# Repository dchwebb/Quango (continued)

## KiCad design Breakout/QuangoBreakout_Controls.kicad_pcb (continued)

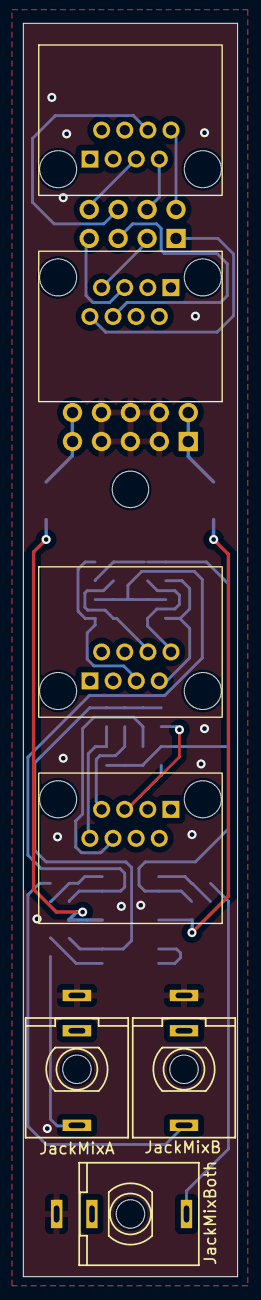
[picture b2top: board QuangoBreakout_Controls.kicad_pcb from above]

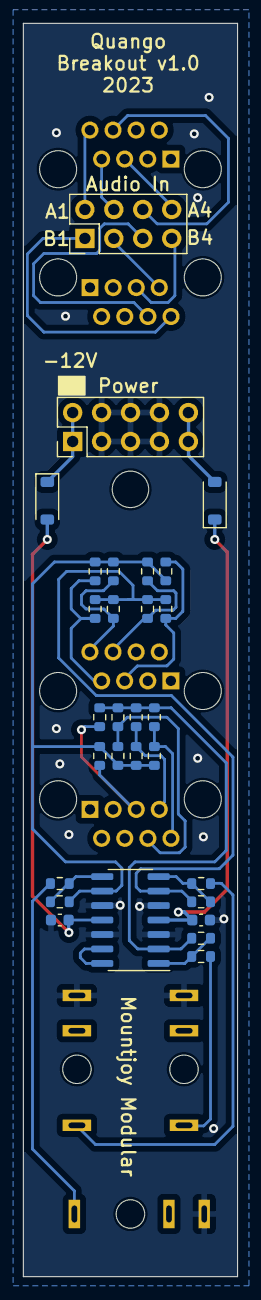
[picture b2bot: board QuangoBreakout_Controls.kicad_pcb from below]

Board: 2 copper layers, 18.8 x 110.0 mm, 37 parts (29 on the bottom side), 31 nets.

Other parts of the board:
H1: MountingHole; MountingHole_3.2mm_M3_ISO14580

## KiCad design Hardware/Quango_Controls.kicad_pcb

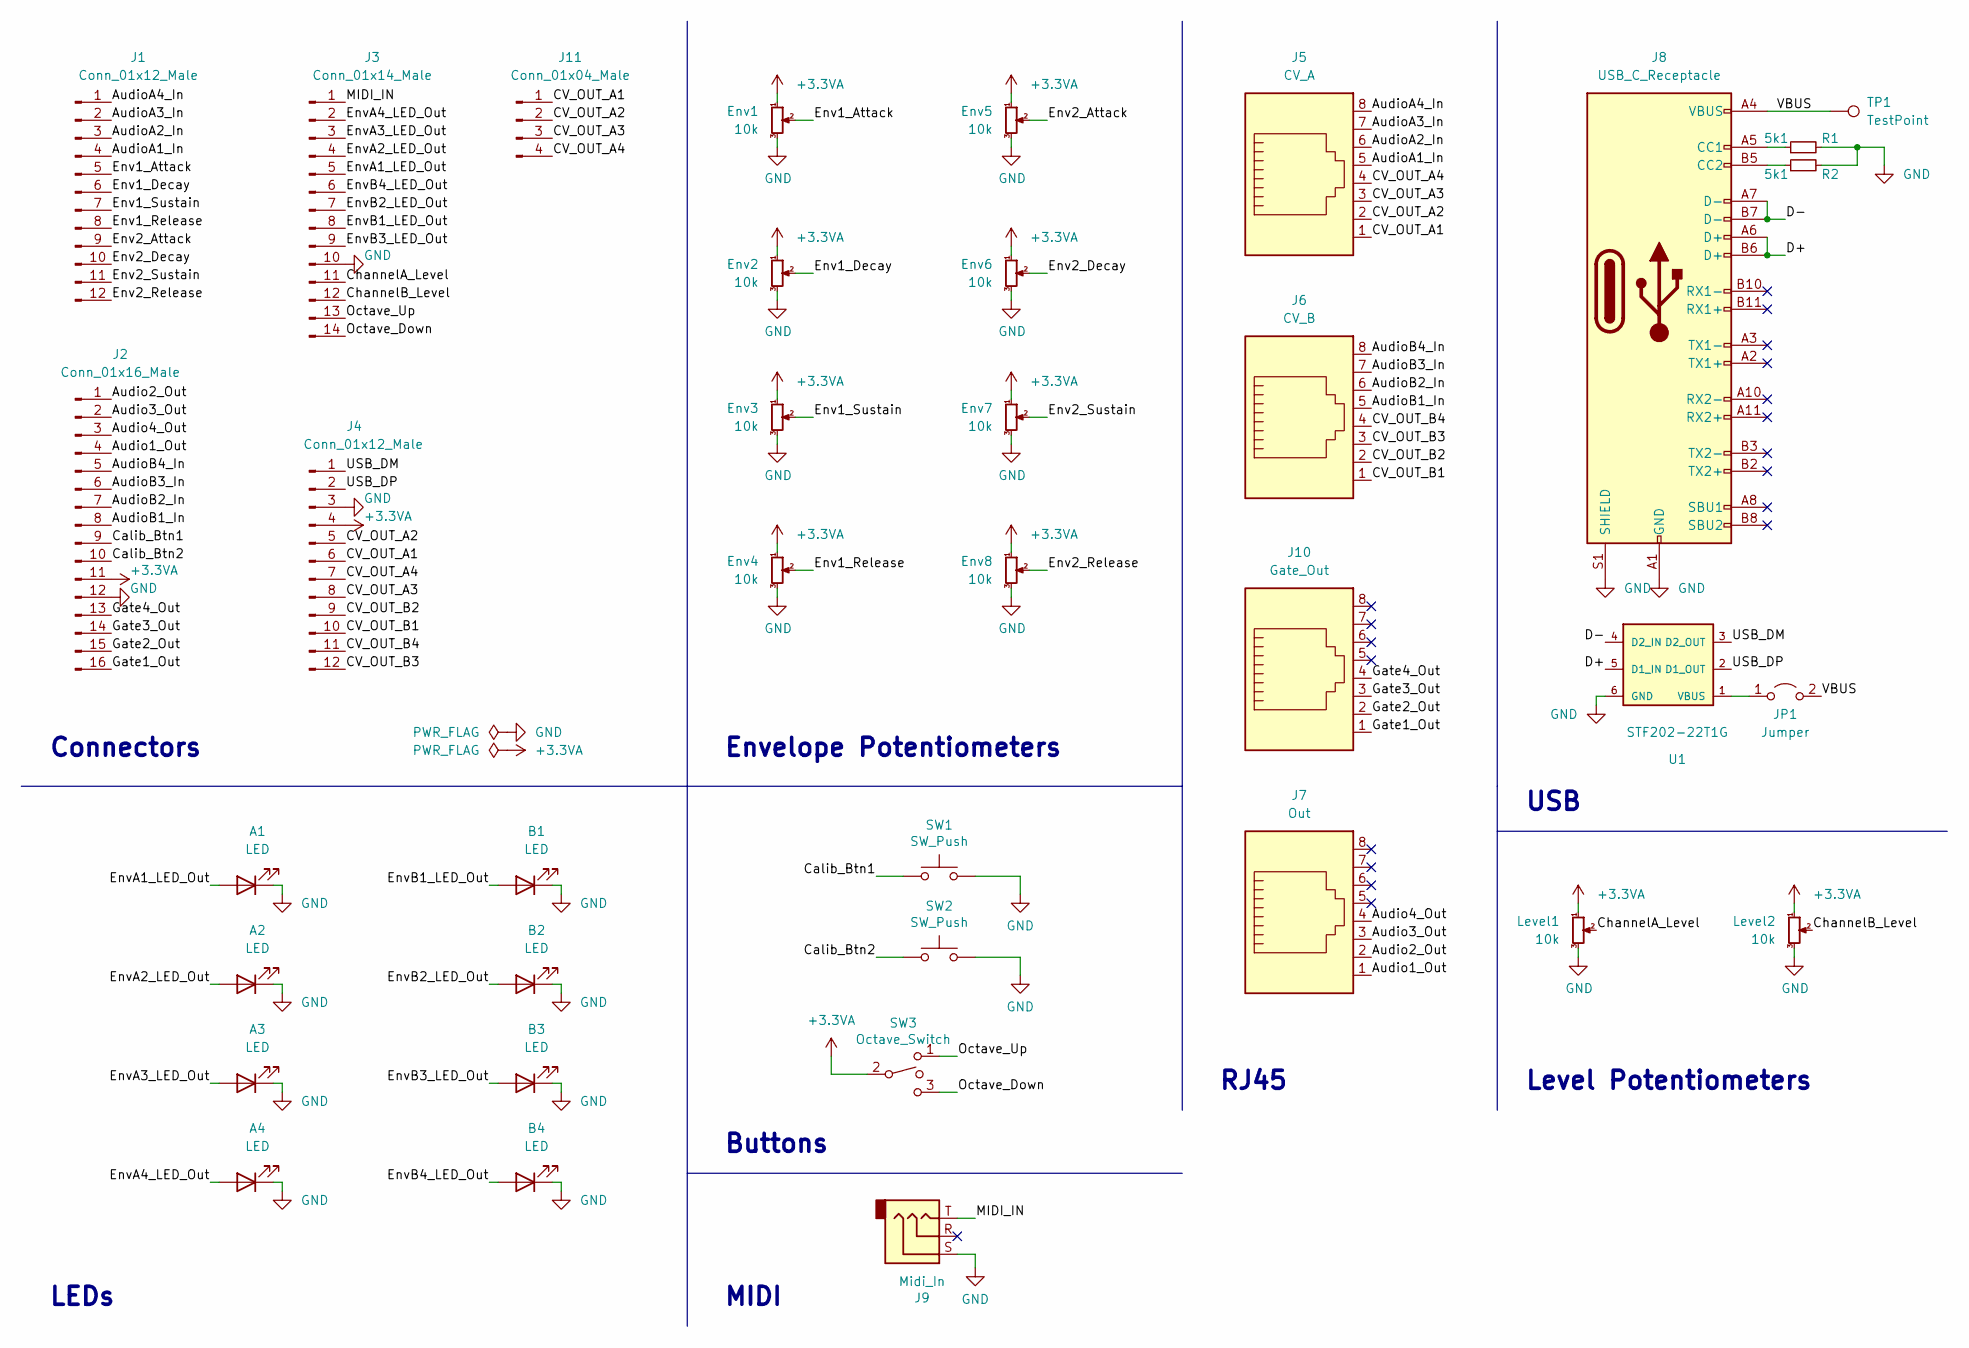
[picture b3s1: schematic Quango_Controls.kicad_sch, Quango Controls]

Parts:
A1, A2, A3, A4: LED; LED_D3.0mm
B1, B2, B3, B4: LED; LED_D3.0mm
Env1, Env2, Env3, Env4, Env5, Env6, Env7, Env8: 10k; Alpha_9mm_Potentiometer_Aligned
J1, J4: Conn_01x12_Male; PinSocket_1x12_P2.54mm_Vertical
J2: Conn_01x16_Male; PinSocket_1x16_P2.54mm_Vertical
J3: Conn_01x14_Male; PinSocket_1x14_P2.54mm_Vertical
J5: CV_A; RJ45_Molex_42878-8506
J6: CV_B; RJ45_Molex_42878-8506
J7: Out; RJ45_Molex_42878-8506
J8: USB_C_Receptacle; USB_C_Receptacle_Amphenol_12401951E412A
J9: Midi_In; Thonkiconn_Stereo-PJ366ST
J10: Gate_Out; RJ45_Molex_42878-8506
J11: Conn_01x04_Male; PinHeader_1x04_P2.54mm_Vertical
JP1: Jumper; SolderJumper-2_P1.3mm_Open_RoundedPad1.0x1.5mm
Level1, Level2: 10k; Potentiometer_Bourns_PTA4543_Single_Slide
R1, R2: 5k1; R_0805_2012Metric
SW1, SW2: SW_Push; SW_PUSH_6mm_aligned
SW3: Octave_Switch; SP3T_Mini_Switch
TP1: TestPoint; PinSocket_1x01_P2.54mm_Vertical
U1: STF202-22T1G

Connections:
+3.3VA: Env1.1, Env2.1, Env3.1, Env4.1, Env5.1, Env6.1, Env7.1, Env8.1, J2.11, J4.4, Level1.1, Level2.1, SW3.2
/Audio1_Out: J2.4, J7.1
/Audio2_Out: J2.1, J7.2
/Audio3_Out: J2.2, J7.3
/Audio4_Out: J2.3, J7.4
/AudioA1_In: J1.4, J5.5
/AudioA2_In: J1.3, J5.6
/AudioA3_In: J1.2, J5.7
/AudioA4_In: J1.1, J5.8
/AudioB1_In: J2.8, J6.5
/AudioB2_In: J2.7, J6.6
/AudioB3_In: J2.6, J6.7
/AudioB4_In: J2.5, J6.8
/CV_OUT_A1: J4.6, J5.1, J11.1
/CV_OUT_A2: J4.5, J5.2, J11.2
/CV_OUT_A3: J4.8, J5.3, J11.3
/CV_OUT_A4: J4.7, J5.4, J11.4
/CV_OUT_B1: J4.10, J6.1
/CV_OUT_B2: J4.9, J6.2
/CV_OUT_B3: J4.12, J6.3
/CV_OUT_B4: J4.11, J6.4
/Calib_Btn1: J2.9, SW1.1
/Calib_Btn2: J2.10, SW2.1
/ChannelA_Level: J3.11, Level1.2
/ChannelB_Level: J3.12, Level2.2
/D+: J8.A6 (D+), J8.B6 (D+), U1.5 (D1_IN)
/D-: J8.A7 (D-), J8.B7 (D-), U1.4 (D2_IN)
/Env1_Attack: Env1.2, J1.5
/Env1_Decay: Env2.2, J1.6
/Env1_Release: Env4.2, J1.8
/Env1_Sustain: Env3.2, J1.7
/Env2_Attack: Env5.2, J1.9
/Env2_Decay: Env6.2, J1.10
/Env2_Release: Env8.2, J1.12
/Env2_Sustain: Env7.2, J1.11
/EnvA1_LED_Out: A1.2 (A), J3.5
/EnvA2_LED_Out: A2.2 (A), J3.4
/EnvA3_LED_Out: A3.2 (A), J3.3
/EnvA4_LED_Out: A4.2 (A), J3.2
/EnvB1_LED_Out: B1.2 (A), J3.8
/EnvB2_LED_Out: B2.2 (A), J3.7
/EnvB3_LED_Out: B3.2 (A), J3.9
/EnvB4_LED_Out: B4.2 (A), J3.6
/Gate1_Out: J2.16, J10.1
/Gate2_Out: J2.15, J10.2
/Gate3_Out: J2.14, J10.3
/Gate4_Out: J2.13, J10.4
/MIDI_IN: J3.1, J9.T
/Octave_Down: J3.14, SW3.3
/Octave_Up: J3.13, SW3.1
/USB_DM: J4.1, U1.3 (D2_OUT)
/USB_DP: J4.2, U1.2 (D1_OUT)
/VBUS: J8.A4 (VBUS), J8.A9 (VBUS), J8.B4 (VBUS), J8.B9 (VBUS), JP1.2 (B), TP1.1
GND: A1.1 (K), A2.1 (K), A3.1 (K), A4.1 (K), B1.1 (K), B2.1 (K), B3.1 (K), B4.1 (K), Env1.3, Env2.3, Env3.3, Env4.3, Env5.3, Env6.3, Env7.3, Env8.3, J2.12, J3.10, J4.3, J8.A1 (GND), J8.A12 (GND), J8.B1 (GND), J8.B12 (GND), J8.S1 (SHIELD), J9.S, Level1.3, Level2.3, R1.2, R2.2, SW1.2, SW2.2, U1.6 (GND)
unnamed: J8.A5 (CC1), R1.1
unnamed: J8.B5 (CC2), R2.1
unnamed: JP1.1 (A), U1.1 (VBUS)

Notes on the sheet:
Buttons
Connectors
RJ45
USB
Level Potentiometers
Envelope Potentiometers
LEDs
MIDI

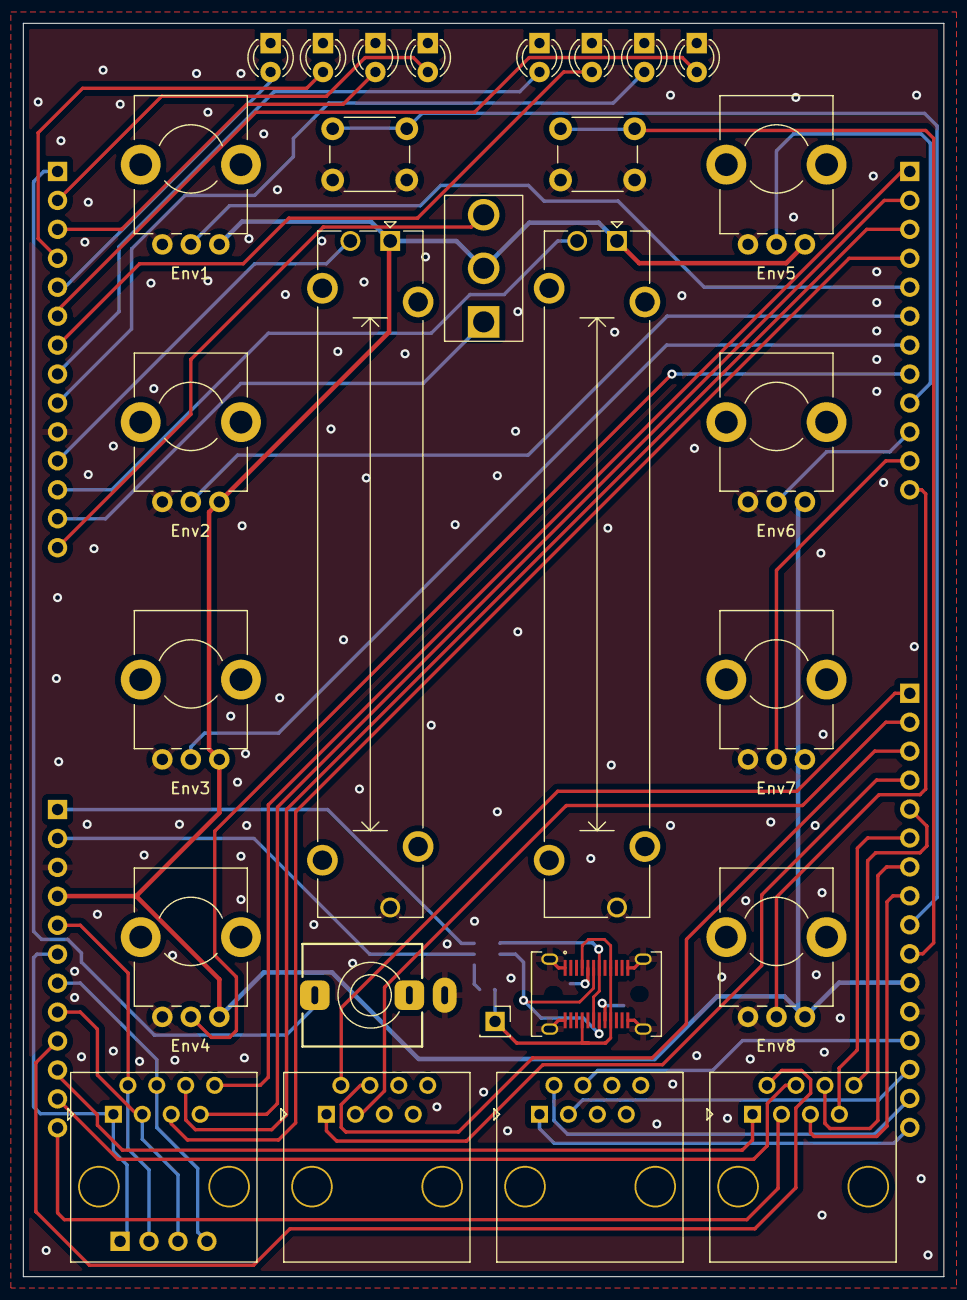
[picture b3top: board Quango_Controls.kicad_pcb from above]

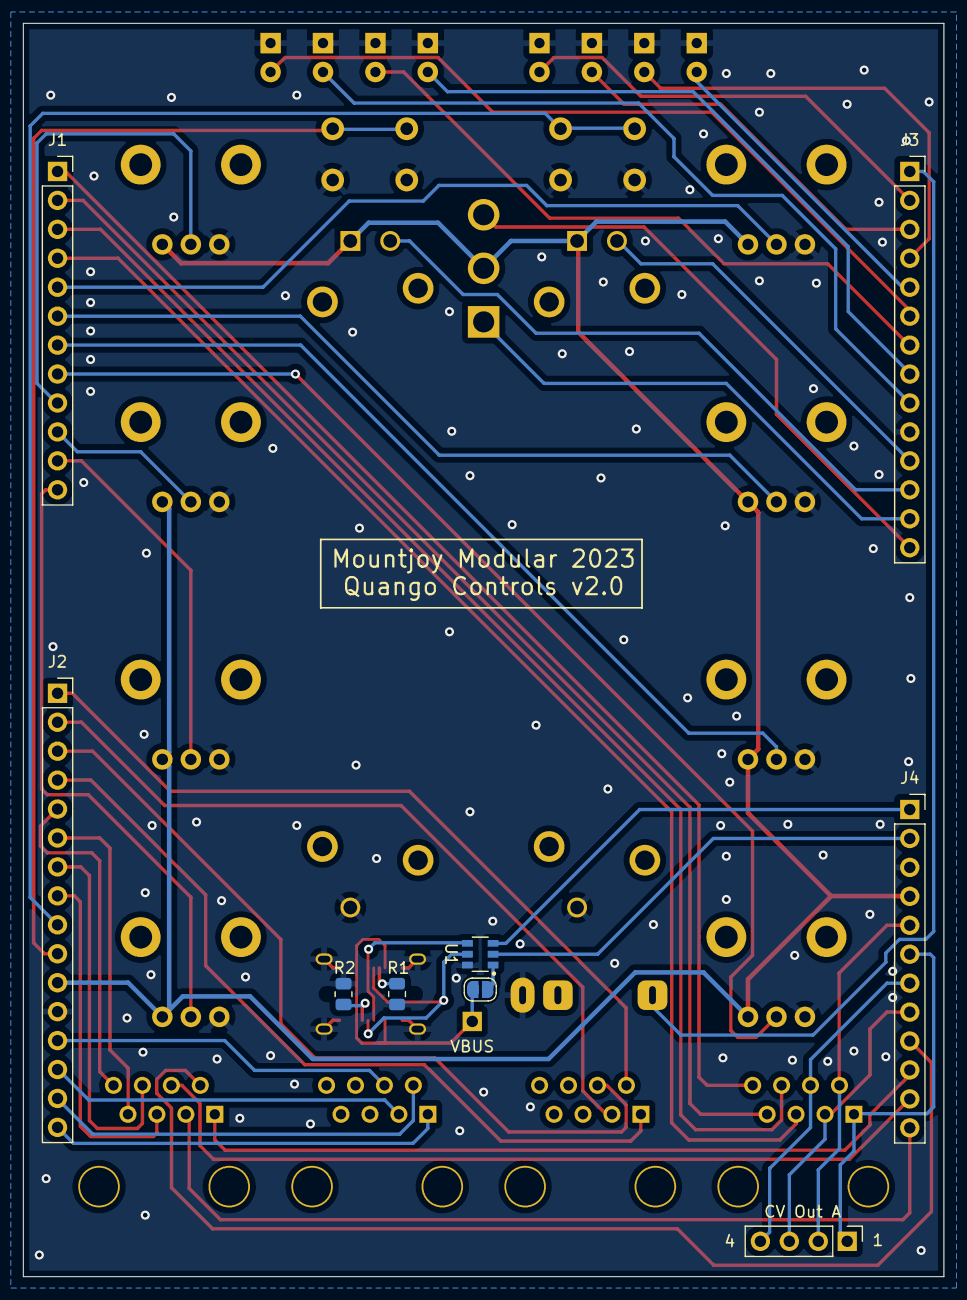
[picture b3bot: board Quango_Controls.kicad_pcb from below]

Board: 2 copper layers, 80.8 x 110.0 mm, 37 parts (9 on the bottom side), 57 nets.

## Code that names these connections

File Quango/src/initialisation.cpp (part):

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
void InitDAC()
{
	// Configure 4 DAC outputs PA4 and PA5 are regular DAC1 buffered outputs; PA2 and PB1 are DAC3 via OpAmp1 and OpAmp3 (Manual p.782)

	RCC->AHB2ENR |= RCC_AHB2ENR_GPIOAEN;			// Enable GPIO Clock
	RCC->AHB2ENR |= RCC_AHB2ENR_GPIOBEN;			// Enable GPIO Clock
	RCC->AHB2ENR |= RCC_AHB2ENR_DAC1EN | RCC_AHB2ENR_DAC2EN | RCC_AHB2ENR_DAC3EN | RCC_AHB2ENR_DAC4EN;				// Enable DAC Clock

	DAC1->MCR &= ~DAC_MCR_MODE1_Msk;				// Set to normal mode: DAC1 channel1 is connected to external pin with Buffer enabled
	DAC1->CR |= DAC_CR_EN1;							// Enable DAC using PA4 (DAC_OUT1)

	DAC1->MCR &= ~DAC_MCR_MODE2_Msk;				// Set to normal mode: DAC1 channel2 is connected to external pin with Buffer enabled
	DAC1->CR |= DAC_CR_EN2;							// Enable DAC using PA5 (DAC_OUT2)

	DAC2->MCR &= ~DAC_MCR_MODE1_Msk;				// Set to normal mode: DAC2 channel1 is connected to external pin with Buffer enabled
	DAC2->CR |= DAC_CR_EN1;							// Enable DAC using PA6 (DAC_OUT1)

	// output triggered with DAC->DHR12R1 = x;

	// Opamp for DAC3 Channel 1: Follower configuration mode - output on PA2
	DAC3->MCR |= DAC_MCR_MODE1_0 | DAC_MCR_MODE1_1;	// 011: DAC channel1 is connected to on chip peripherals with Buffer disabled
	DAC3->CR |= DAC_CR_EN1;							// Enable DAC

	OPAMP1->CSR |= OPAMP_CSR_VMSEL;					// 11: Opamp_out connected to OPAMPx_VINM input
	OPAMP1->CSR |= OPAMP_CSR_VPSEL;					// 11: DAC3_CH1  connected to OPAMP1 VINP input
	OPAMP1->CSR |= OPAMP_CSR_OPAMPxEN;				// Enable OpAmp: voltage on pin OPAMPx_VINP is buffered to pin OPAMPx_VOUT (PA2)

	// Opamp for DAC3 Channel 2: Follower configuration mode - output on PB1
	DAC3->MCR |= DAC_MCR_MODE2_0 | DAC_MCR_MODE2_1;	// 011: DAC channel2 is connected to on chip peripherals with Buffer disabled
	DAC3->CR |= DAC_CR_EN2;							// Enable DAC

	OPAMP3->CSR |= OPAMP_CSR_VMSEL;					// 11: Opamp_out connected to OPAMPx_VINM input
	OPAMP3->CSR |= OPAMP_CSR_VPSEL;					// 11: DAC3_CH2  connected to OPAMP1 VINP input
	OPAMP3->CSR |= OPAMP_CSR_OPAMPxEN;				// Enable OpAmp: voltage on pin OPAMPx_VINP is buffered to pin OPAMPx_VOUT (PB1)

	// Opamp for DAC4 Channel 1: Follower configuration mode - output on PB12
	DAC4->MCR |= DAC_MCR_MODE1_0 | DAC_MCR_MODE1_1;	// 011: DAC channel1 is connected to on chip peripherals with Buffer disabled
	DAC4->CR |= DAC_CR_EN1;							// Enable DAC

	OPAMP4->CSR |= OPAMP_CSR_VMSEL;					// 11: Opamp_out connected to OPAMPx_VINM input
	OPAMP4->CSR |= OPAMP_CSR_VPSEL;					// 11: DAC4_CH1  connected to OPAMP1 VINP input
	OPAMP4->CSR |= OPAMP_CSR_OPAMPxEN;				// Enable OpAmp: voltage on pin OPAMPx_VINP is buffered to pin OPAMPx_VOUT (PB12)

	// Opamp for DAC4 Channel 2: Follower configuration mode - output on PA8
	DAC4->MCR |= DAC_MCR_MODE2_0 | DAC_MCR_MODE2_1;	// 011: DAC channel2 is connected to on chip peripherals with Buffer disabled
	DAC4->CR |= DAC_CR_EN2;							// Enable DAC

	OPAMP5->CSR |= OPAMP_CSR_VMSEL;					// 11: Opamp_out connected to OPAMPx_VINM input
	OPAMP5->CSR |= OPAMP_CSR_VPSEL;					// 11: DAC4_CH2  connected to OPAMP1 VINP input
	OPAMP5->CSR |= OPAMP_CSR_OPAMPxEN;				// Enable OpAmp: voltage on pin OPAMPx_VINP is buffered to pin OPAMPx_VOUT (PA8)

}

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	RCC->AHB2ENR |= RCC_AHB2ENR_GPIODEN;			// GPIO D clock
	RCC->AHB2ENR |= RCC_AHB2ENR_GPIOFEN;			// GPIO F clock

	//	Init Multiplexer pins PA1, PA3, PF2
	GPIOA->MODER &= ~GPIO_MODER_MODER1_1;			// PA1: Multiplexer A0 out
	GPIOA->MODER &= ~GPIO_MODER_MODER3_1;			// PA3: Multiplexer A1 out
	GPIOF->MODER &= ~GPIO_MODER_MODER2_1;			// PF2: Multiplexer A2 out

	// Init Gate outputs PD2 - PD5
	GPIOD->MODER &= ~GPIO_MODER_MODER2_1;			// PD2: Gate1 Out
	GPIOD->MODER &= ~GPIO_MODER_MODER3_1;			// PD3: Gate2 Out
	GPIOD->MODER &= ~GPIO_MODER_MODER4_1;			// PD4: Gate3 Out
	GPIOD->MODER &= ~GPIO_MODER_MODER5_1;			// PD5: Gate4 Out

	// Calibration buttons input
	GPIOB->MODER &= ~GPIO_MODER_MODER10;			// PB10: channel A
	GPIOB->PUPDR |= GPIO_PUPDR_PUPD10_0;			// Activate pull-up
	GPIOB->MODER &= ~GPIO_MODER_MODER11;			// PB11: channel B
	GPIOB->PUPDR |= GPIO_PUPDR_PUPD11_0;			// Activate pull-up

	// Octave Switch pins PD0, PC12
	GPIOD->MODER &= ~GPIO_MODER_MODER0;				// PD0: Octave
	GPIOD->PUPDR |= GPIO_PUPDR_PUPD0_1;				// Activate pull-down
	GPIOC->MODER &= ~GPIO_MODER_MODER12;			// PC12: Octave
	GPIOC->PUPDR |= GPIO_PUPDR_PUPD12_1;			// Activate pull-down
}

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void InitSPI1()
{
	// Controls AD5676 8 channel DAC
	// PB3: SPI1_SCK; PB4: SPI1_MISO; PB5: SPI1_MOSI; PA15: SPI1_NSS (AF5)
	RCC->APB2ENR |= RCC_APB2ENR_SPI1EN;			// SPI1 clock enable
	RCC->AHB2ENR |= RCC_AHB2ENR_GPIOAEN | RCC_AHB2ENR_GPIOBEN;			// GPIO clocks

	// PB3: SPI1_SCK
	GPIOB->MODER  &= ~GPIO_MODER_MODE3_0;			// 10: Alternate function mode
	GPIOB->AFR[0] |= 5 << GPIO_AFRL_AFSEL3_Pos;		// Alternate Function 5 (SPI1)

	// PB5: SPI1_MOSI
	GPIOB->MODER  &= ~GPIO_MODER_MODE5_0;			// 10: Alternate function mode
	GPIOB->AFR[0] |= 5 << GPIO_AFRL_AFSEL5_Pos;		// Alternate Function 5 (SPI1)

	// PA15: SPI1_NSS (uses GPIO rather than hardware NSS which doesn't work with 24 bit data)
	GPIOA->MODER |= GPIO_MODER_MODE15_0;			// 01: Output mode
	GPIOA->MODER &= ~GPIO_MODER_MODE15_1;			// 01: Output mode

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void InitSPI2()
{
	// Controls MCP48CMB21 single channel DAC for channel B envelope 4
	// PA10: SPI2_MISO; PB13: SPI2_SCK; PB15: SPI2_MOSI; PD15: SPI2_NSS
	RCC->APB1ENR1 |= RCC_APB1ENR1_SPI2EN;			// SPI2 clock enable
	RCC->AHB2ENR |= RCC_AHB2ENR_GPIOAEN | RCC_AHB2ENR_GPIOBEN | RCC_AHB2ENR_GPIODEN;			// GPIO clocks

	// PB13: SPI2_SCK
	GPIOB->MODER  &= ~GPIO_MODER_MODE13_0;			// 10: Alternate function mode
	GPIOB->AFR[1] |= 5 << GPIO_AFRH_AFSEL13_Pos;	// Alternate Function 5 (SPI2)

	// PB15: SPI2_MOSI
	GPIOB->MODER  &= ~GPIO_MODER_MODE15_0;			// 10: Alternate function mode
	GPIOB->AFR[1] |= 5 << GPIO_AFRH_AFSEL15_Pos;	// Alternate Function 5 (SPI2)

	// PD15: SPI2_NSS
	GPIOD->MODER  &= ~GPIO_MODER_MODE15_1;			// 01: Output mode

	// Configure SPI
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
void InitMidiUART()
{
	// PC11: UART4_RX (AF5) or USART3_RX (AF7)

	RCC->APB1ENR1 |= RCC_APB1ENR1_UART4EN;			// UART4 clock enable
	RCC->AHB2ENR |= RCC_AHB2ENR_GPIOCEN;			// GPIO port C

	GPIOC->MODER &= ~GPIO_MODER_MODE11_0;			// Set alternate function on PE0
	GPIOC->AFR[1] |= 5 << GPIO_AFRH_AFSEL11_Pos;	// Alternate function on PC11 for USART4_RX is AF5

	// By default clock source is muxed to peripheral clock 1 which is system clock
	// Calculations depended on oversampling mode set in CR1 OVER8. Default = 0: Oversampling by 16
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
void InitPWMTimer()
{
	// TIM3: Channel 1: PE2 (AF2)
	// 		 Channel 2: PE3 (AF2)
	// 		 Channel 3: PE4 (AF2)
	// 		 Channel 4: PE5 (AF2)
	RCC->AHB2ENR |= RCC_AHB2ENR_GPIOEEN;			// Enable GPIO Clock
	RCC->APB1ENR1 |= RCC_APB1ENR1_TIM3EN;

	// Enable channels 1 - 4 PWM output pins on PE2-5
	GPIOE->MODER &= ~(GPIO_MODER_MODE2_0 | GPIO_MODER_MODE3_0 | GPIO_MODER_MODE4_0 | GPIO_MODER_MODE5_0);
	GPIOE->AFR[0] |= GPIO_AFRL_AFSEL2_1 | GPIO_AFRL_AFSEL3_1 | GPIO_AFRL_AFSEL4_1 | GPIO_AFRL_AFSEL5_1;			// AF2

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	TIM3->CR1 |= TIM_CR1_CEN;						// Enable counter

	//////////////////////////////////////////////////////////////////////////////////////////////////////////////////
	// TIM4: PD12 TIM4_CH1 (AF2)
	// 		 PD13 TIM4_CH2 (AF2)
	// 		 PD14 TIM4_CH3 (AF2)
	// 		 PB9  TIM4_CH4 (AF2)
	RCC->AHB2ENR |= RCC_AHB2ENR_GPIOBEN;			// Enable GPIO Clock
	RCC->AHB2ENR |= RCC_AHB2ENR_GPIODEN;			// Enable GPIO Clock
	RCC->APB1ENR1 |= RCC_APB1ENR1_TIM4EN;

	// Enable channels 1 - 3 PWM output pins on PD12-14
	GPIOD->MODER &= ~(GPIO_MODER_MODE12_0 | GPIO_MODER_MODE13_0 | GPIO_MODER_MODE14_0);
	GPIOD->AFR[1] |= GPIO_AFRH_AFSEL12_1 | GPIO_AFRH_AFSEL13_1 | GPIO_AFRH_AFSEL14_1;			// AF2

	// Enable channel 4 PWM output pin on PB9
	GPIOB->MODER &= ~GPIO_MODER_MODE9_0;
	GPIOB->AFR[1] |= GPIO_AFRH_AFSEL9_1;			// AF2

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
/*--------------------------------------------------------------------------------------------
Configure ADC Channels to be converted:
0	PE7 ADC3_IN4		Env1 Attack
1	PE8 ADC345_IN6		Env1 Decay
2	PE9 ADC3_IN2		Env1 Sustain
3	PE10 ADC345_IN14	Env1 Release

4	PE11 ADC345_IN15	Env2 Attack
5	PE12 ADC345_IN16	Env2 Decay
6	PE14 ADC4_IN1		Env2 Sustain
7	PE15 ADC4_IN2		Env2 Release

8	PC0 ADC12_IN6		Pitch Detect Audio
*/

void InitADC1(volatile uint16_t* buffer, uint16_t channels)
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
	/*
	Configure ADC Channels to be converted:
	PC0 ADC12_IN6		Pitch Detect Audio
	PC2 ADC12_IN8		ChannelALevel
	*/

	InitAdcPins(ADC1, {6, 8});
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
	/*--------------------------------------------------------------------------------------------
	Configure ADC Channels to be converted:
	PE7 ADC3_IN4		Env1 Attack
	PE8 ADC345_IN6		Env1 Decay
	PE9 ADC3_IN2		Env1 Sustain
	PE10 ADC345_IN14	Env1 Release
	*/

	InitAdcPins(ADC3, {4, 6, 2, 14});
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
	/*--------------------------------------------------------------------------------------------
	Configure ADC Channels to be converted:
	PD9 ADC4_IN13 		ChannelBLevel
	PE11 ADC345_IN15	Env2 Attack
	PE12 ADC345_IN16	Env2 Decay
	PE14 ADC4_IN1		Env2 Sustain
	PE15 ADC4_IN2		Env2 Release
	*/

	InitAdcPins(ADC4, {13, 15, 16, 1, 2});
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
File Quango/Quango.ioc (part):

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Mcu.Name=STM32G473V(B-C-E)Tx
Mcu.Package=LQFP100
Mcu.UserName=STM32G473VETx
PA11.Mode=Device
PA11.Signal=USB_DM
PA12.Mode=Device
PA12.Signal=USB_DP
PC0.Mode=IN6-Single-Ended
PC0.Signal=ADC1_IN6
PE10.Mode=IN14-Single-Ended
PE10.Signal=ADC3_IN14
PE7.Mode=IN4-Single-Ended
PE7.Signal=ADC3_IN4
PE8.Mode=IN6-Single-Ended
PE8.Signal=ADC3_IN6
PE9.Mode=IN2-Single-Ended
PE9.Signal=ADC3_IN2
PF0-OSC_IN.Mode=HSE-External-Oscillator
PF0-OSC_IN.Signal=RCC_OSC_IN
PF1-OSC_OUT.Mode=HSE-External-Oscillator
PF1-OSC_OUT.Signal=RCC_OSC_OUT
RCC.HSE_VALUE=12000000
RCC.SYSCLKFreq_VALUE=170000000
RCC.SYSCLKSource=RCC_SYSCLKSOURCE_PLLCLK
board=custom

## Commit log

2023-04-20 Schematic Updates
2023-04-21 Added LEDs & Sliders
2023-04-24 More schematic updates
2023-05-06 Moved OpAmps to separate schematic page
2023-05-06 Started laying out component PCB
2023-05-07 Started op-amp layout
2023-05-07 Layout of audio vca section
2023-05-08 Further Layout
2023-05-10 Main components positioned
2023-05-10 Added LED resistors
2023-05-11 More Layout
2023-05-15 First draft of signal routing done
2023-05-16 Started laying out control board
2023-05-16 Reduced module size to 14HP; updated to Amphenol USB C
2023-05-16 Added individual audio channel breakout
2023-05-17 Routing Power traces
2023-05-17 Added Test Points
2023-05-17 Preparing panel and control board for routing
2023-05-18 First draft routing of control board
2023-05-18 Cleaned up Components schematic
2023-05-18 Schematic Clean Up
2023-05-19 Added Gate ouputs to component board
2023-05-19 Updating Controls and Panel to support gates
2023-05-20 Increased size to 16HP
2023-05-20 Added breakout for gates on component board
2023-05-21 Fixed OpAmp Power supply; component board annotations
2023-05-21 Clean Up of Panel and Control boards
2023-05-22 Set up JLC parts placement details
2023-05-22 Updates to Panel Graphics
2023-05-23 Final Updates for v1.0 production
2023-06-02 Created Firmware project and configured clock
2023-06-02 Internal DAC channels tested working; Removed HAL libraries
2023-06-02 ADC1 and SysTick configured and working
2023-06-02 ADC 1, 3, 4 configured and working
2023-06-03 Timer 3 LED PWM configured and working
2023-06-03 Timer 4 PWM Configured and Working
2023-06-03 MIDI UART Configured and working
2023-06-03 USB Serial configured and working
2023-06-03 Started adding SPI2 DAC Control
2023-06-04 Configured SPI1; testing 24 bit output and hardware NSS
2023-06-04 SPI2 single channel DAC working
2023-06-05 Multiplexer tested working; PCB bug - U14 power rails inverted
2023-06-05 AD5676 on SPI1 configured and tested working on channels 1, 2 and 8
2023-06-07 Started implementing voice and envelope handling mechanism
2023-06-07 Voice manager initialises envelope information
2023-06-07 Basic MIDI note on/off > envelope working
2023-06-08 Gate mechanism working
2023-06-08 Envelopes and VCAs tested working for both channels
2023-06-08 Started adding pitch DAC functionality
2023-06-09 Basic pitch handling working on both channels
2023-06-09 Refined gate and envelope handling to retrigger correctly when note stealing
2023-06-09 Implemented basic pitchbend
2023-06-11 Started adding calibration functionality
2023-06-12 Basic calibration tuner functionality working
2023-06-13 Calibration detection code first draft
2023-06-13 Calibration now applied to pitch CV
2023-06-14 Added option to print calibration settings in console
2023-06-14 Calibration works on both channels
2023-06-14 Implemented fader levels
2023-06-14 Both channels can trigger gates (previously just channel A)
2023-06-15 Fixed some volatile issues at higher compiler optimisation level
2023-06-15 Started implementing USB MIDI
2023-06-15 Started reworking USB descriptor handling
2023-06-15 Updated descriptor handling
2023-06-16 Added UART output for outputting USB debug info
2023-06-16 Now enumerating as USB CDC+MIDI device
2023-06-18 Updated CDC Handler
2023-06-18 Updated USB request format
2023-06-18 CDC line coding done in CDCHandler
2023-06-18 Serial handler fully replaced with CDC handler
2023-06-18 Preparing for class-based endpoint activation
2023-06-18 Started reorganising PMA allocation and endpoint activation
    Still issues setting PMA addresses for EP0
2023-06-19 PMA Addresses configured correctly
2023-06-19 USB MIDI working; PMA addresses auto-generated
2023-06-19 USB Code clean up
2023-06-19 USB receive buffers now handled at class level
2023-06-19 Disabled USB debug UART
2023-06-19 Tx/In buffers now class specific
2023-06-20 Tweaks to improve calibration
2023-06-20 Added LED brightness curve; ensure all notes off before calibrating
2023-06-20 Added monophonic mode for voice calibration
2023-06-20 Increased CV output range from 6v - 7.13v to increase maximum output octave
2023-06-21 Calibration config saved to internal Flash
2023-06-22 Added support for long press calibration button to clear calibration offsets
2023-06-23 Altered interrupt priority as some UART MIDI notes were being missed
    Note this could cause issues as midi note may fire setting envelope gate state which will then be overwritten in the envelope calculation.
    Also increased envelope timer frequency to 20kHz.
2023-06-23 Created MIDI note queue; optimisation to envelope calculations
2023-06-23 General code clean up
2023-06-23 Tweaks to calibration; tested over 4 octave range
2023-06-23 Removed calibration volatile testing
2023-06-25 Started designing breakout send/receive board
2023-06-25 Updated to Kicad 7.05
2023-06-25 Laid out breakout panel
2023-06-25 Terminated unused op-amp
2023-06-26 Panel labelling
2023-06-29 Updated controls to include octave switching; revised panel
2023-07-06 Prepared v2 controls and panel for manufacture
2023-07-06 Added header on control board for CV output
2023-07-06 Added Breakout gerbers; Added pdfs of schematics
2023-07-15 Implemented octave up/down switch
    Toggle CS on SPI2 to fix intermittent issue with external DAC
2023-08-04 Added Readme
2023-08-18 Panel version 3
2023-08-19 Updated graphics
2023-09-14 Added v3 panel gerbers
2023-10-23 Maximum release activates 'drone' mode ie stays at current level
2023-10-23 Updated USB class
2023-10-23 Fixed bug with calibration button presses
2023-10-23 Fixed bug in config saving where config page would overrun
2023-10-24 Started implementing interpolated calibration table
2023-10-25 Interpolated calibration working
2023-10-28 Fixed bug in calibration not clearing offsets before running
2024-06-13 Starting to prepare component schematic
2024-10-02 Fixed bug overflow and interrupt priority bug in midi queue handling
2024-10-02 Updated component schematic/pcb to v2
    Kicad 8.0
    Fixing opamp U14 power reversal
